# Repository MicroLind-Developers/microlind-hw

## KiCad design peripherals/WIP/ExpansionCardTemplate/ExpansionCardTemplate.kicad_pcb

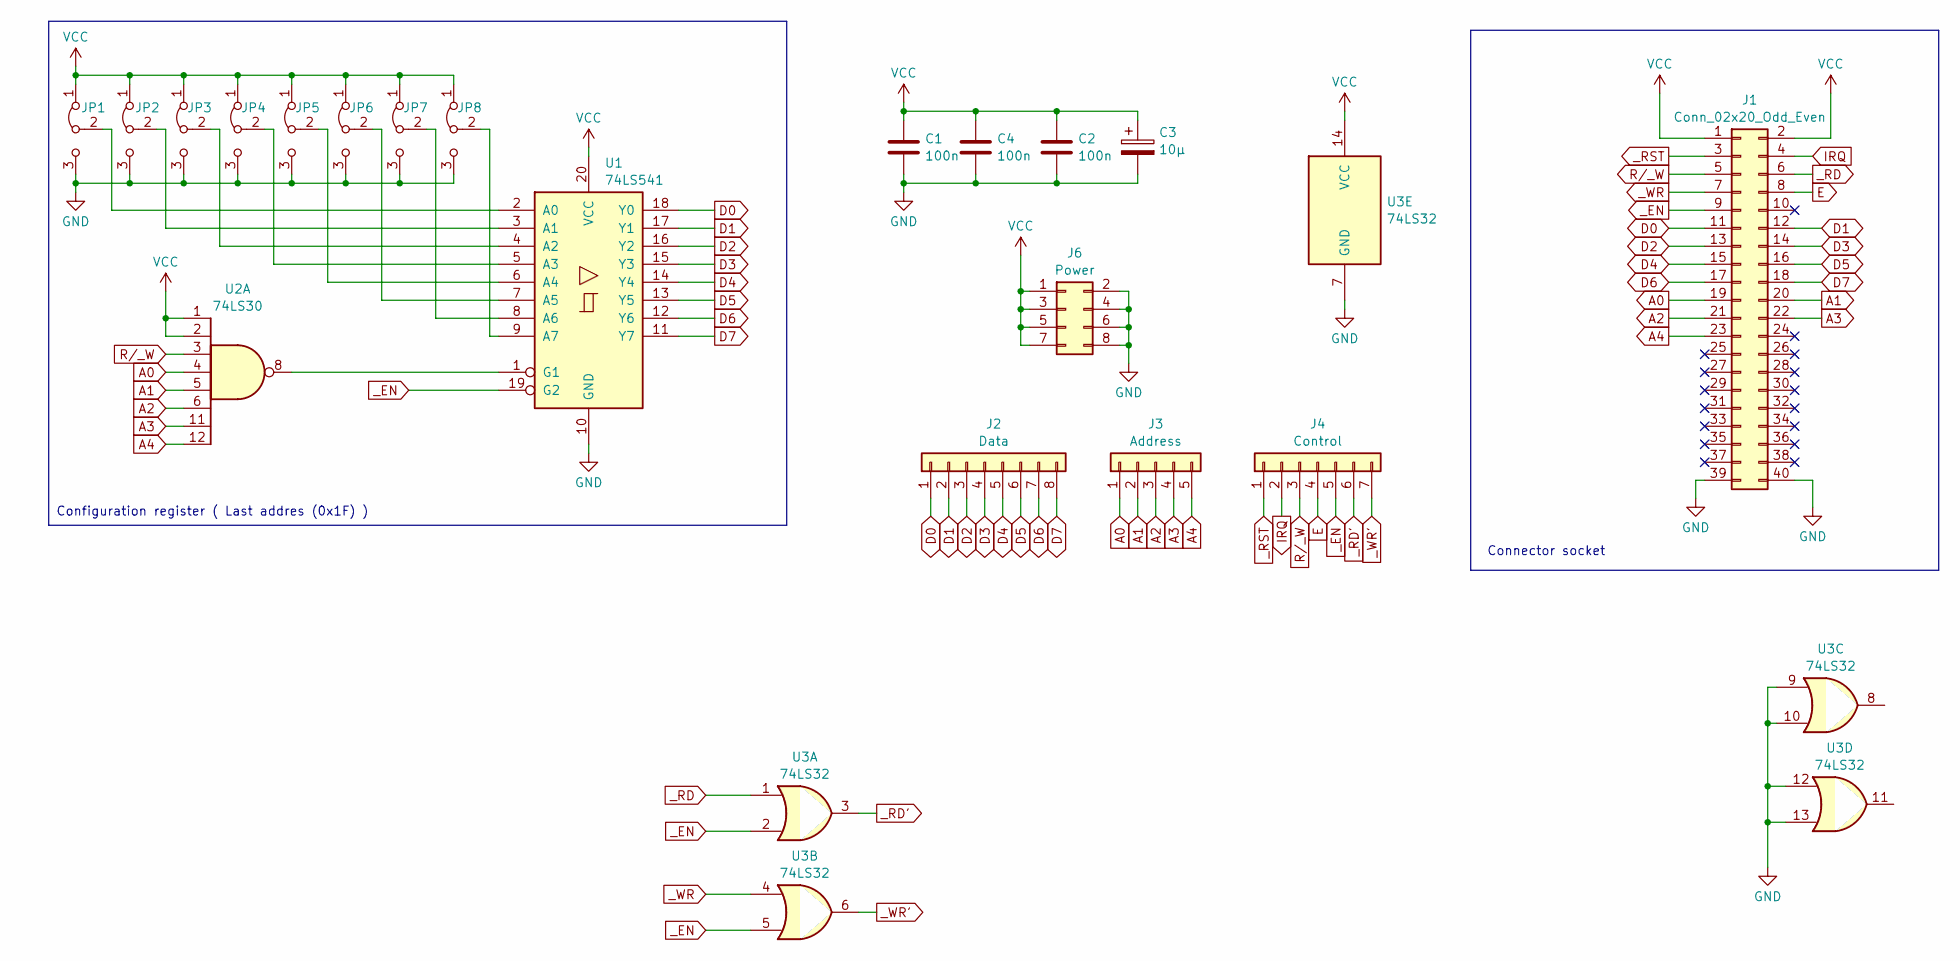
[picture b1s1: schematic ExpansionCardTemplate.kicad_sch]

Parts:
C1, C2, C4: 100n; C_Disc_D3.0mm_W2.0mm_P2.50mm
C3: 10µ; CP_Radial_D4.0mm_P2.00mm
J1: Conn_02x20_Odd_Even; PinHeader_2x20_P2.54mm_Horizontal
J2: Data; PinSocket_1x08_P2.54mm_Vertical
J3: Address; PinSocket_1x05_P2.54mm_Vertical
J4: Control; PinSocket_1x07_P2.54mm_Vertical
J6: Power; PinSocket_2x04_P2.54mm_Vertical
JP1, JP2, JP3, JP4, JP5, JP6, JP7, JP8: Jumper_3_Bridged12; SolderJumper-3_P1.3mm_Open_RoundedPad1.0x1.5mm_NumberLabels
U1: 74LS541; DIP-20_W7.62mm
U2: 74LS30; DIP-12_W7.62mm
U3: 74LS32; DIP-14_W7.62mm

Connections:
A0: J1.19, J3.1, U2.4
A1: J1.20, J3.2, U2.5
A2: J1.21, J3.3, U2.6
A3: J1.22, J3.4, U2.11
A4: J1.23, J3.5, U2.12
D0: J1.11, J2.1, U1.18 (Y0)
D1: J1.12, J2.2, U1.17 (Y1)
D2: J1.13, J2.3, U1.16 (Y2)
D3: J1.14, J2.4, U1.15 (Y3)
D4: J1.15, J2.5, U1.14 (Y4)
D5: J1.16, J2.6, U1.13 (Y5)
D6: J1.17, J2.7, U1.12 (Y6)
D7: J1.18, J2.8, U1.11 (Y7)
E: J1.8, J4.4
GND: C1.2, C2.2, C3.2, C4.2, J1.39, J1.40, J6.2, J6.4, J6.6, J6.8, JP1.3 (B), JP2.3 (B), JP3.3 (B), JP4.3 (B), JP5.3 (B), JP6.3 (B), JP7.3 (B), JP8.3 (B), U1.10 (GND), U3.7 (GND), U3.9, U3.10, U3.12, U3.13
IRQ: J1.4, J4.2
unnamed: JP1.2 (C), U1.2 (A0)
unnamed: JP2.2 (C), U1.3 (A1)
unnamed: JP3.2 (C), U1.4 (A2)
unnamed: JP4.2 (C), U1.5 (A3)
unnamed: JP5.2 (C), U1.6 (A4)
unnamed: JP6.2 (C), U1.7 (A5)
unnamed: JP7.2 (C), U1.8 (A6)
unnamed: JP8.2 (C), U1.9 (A7)
unnamed: U1.1 (G1), U2.8
R/_W: J1.5, J4.3, U2.3
VCC: C1.1, C2.1, C3.1, C4.1, J1.1, J1.2, J6.1, J6.3, J6.5, J6.7, JP1.1 (A), JP2.1 (A), JP3.1 (A), JP4.1 (A), JP5.1 (A), JP6.1 (A), JP7.1 (A), JP8.1 (A), U1.20 (VCC), U2.1, U2.2, U3.14 (VCC)
_EN: J1.9, J4.5, U1.19 (G2), U3.2, U3.5
_RD: J1.6, U3.1
_RD': J4.6, U3.3
_RST: J1.3, J4.1
_WR: J1.7, U3.4
_WR': J4.7, U3.6

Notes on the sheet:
Configuration register ( Last addres (0x1F) )
Connector socket

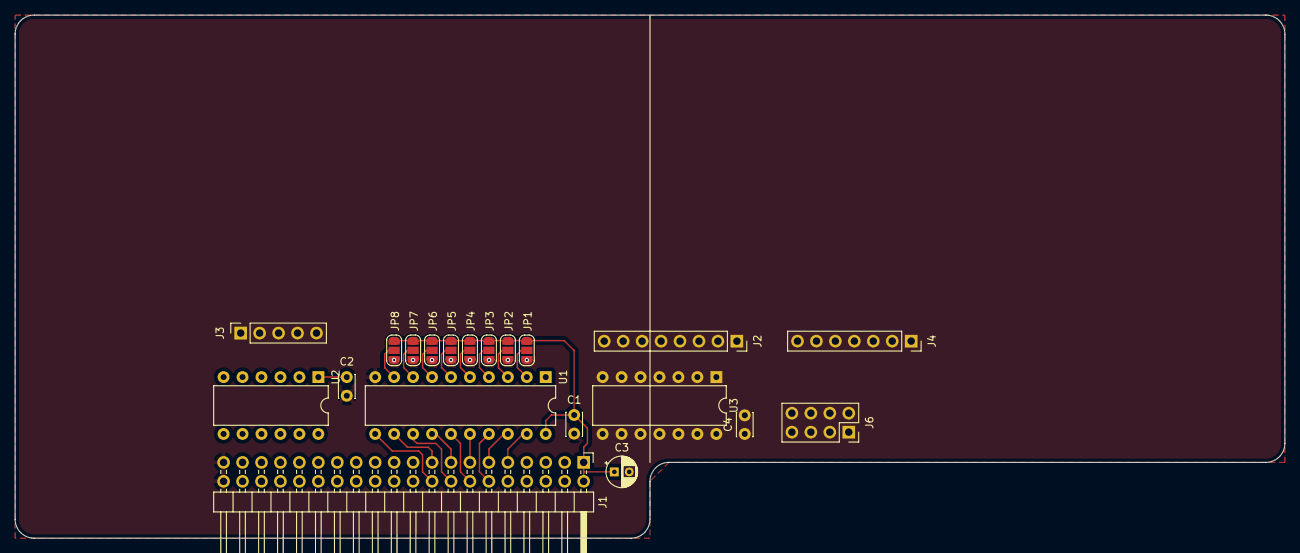
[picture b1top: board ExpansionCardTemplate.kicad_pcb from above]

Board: 2 copper layers, 170.2 x 70.1 mm, 20 parts (0 on the bottom side), 33 nets.

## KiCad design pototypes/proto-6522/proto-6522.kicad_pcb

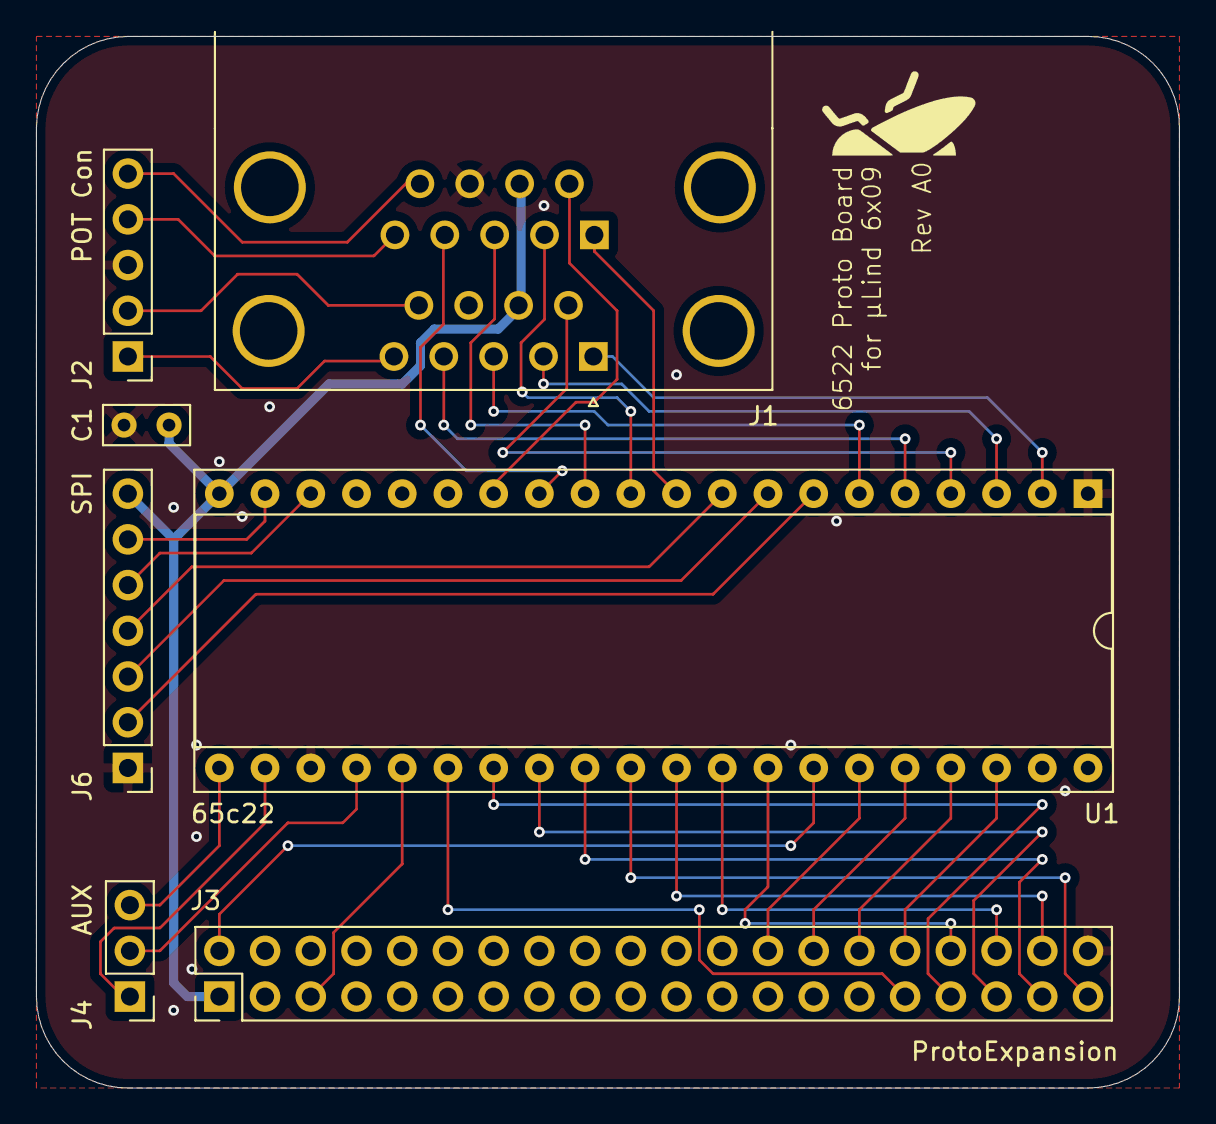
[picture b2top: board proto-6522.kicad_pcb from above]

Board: 2 copper layers, 63.5 x 58.4 mm, 7 parts (0 on the bottom side), 38 nets.

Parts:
C1: C; C_Rect_L4.6mm_W2.0mm_P2.50mm_MKS02_FKP02
J1: DSUB-9-Double_NorComp
J2: POT Con; PinHeader_1x05_P2.54mm_Vertical
J3: ProtoExpansion; PinHeader_2x20_P2.54mm_Vertical
J4: AUX; PinHeader_1x03_P2.54mm_Vertical
J6: SPI; PinHeader_1x07_P2.54mm_Vertical
U1: 65c22; DIP-40_W15.24mm_Socket

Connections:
/A0: J3.32, U1.38 (RS0)
/A1: J3.30, U1.37 (RS1)
/A2: J3.28, U1.36 (RS2)
/A3: J3.26, U1.35 (RS3)
/COPI/CIPO: J6.6, U1.19 (CB2)
/CS0: J6.2, U1.7 (PA5)
/CS1: J6.3, U1.8 (PA6)
/CS2: J6.4, U1.9 (PA7)
/D0: J3.34, U1.33 (D0)
/D1: J3.36, U1.32 (D1)
/D2: J3.38, U1.31 (D2)
/D3: J3.39, U1.30 (D3)
/D4: J3.37, U1.29 (D4)
/D5: J3.35, U1.28 (D5)
/D6: J3.33, U1.27 (D6)
/D7: J3.31, U1.26 (D7)
/E: J3.5, U1.25 (ϕ2)
/R/~W: J4.1, U1.22 (R/~W)
/SCK: J6.5, U1.18 (CB1)
/~INT_PAR: J4.3, U1.21 (~IRQ)
/~PAR_EN: J4.2, U1.24 (CS1)
/~RST: J3.2, U1.34 (~RES)
GND: C1.2, J1.8, J1.18, J2.3, J3.40, J6.1, U1.1 (VSS), U1.23 (~CS2)
unnamed: J1.5, J2.1
unnamed: J1.9, J2.2
unnamed: J1.15, J2.4
unnamed: J1.19, J2.5
unnamed: J1.1, U1.2 (PA0)
unnamed: J1.2, U1.3 (PA1)
unnamed: J1.6, U1.4 (PA2)
unnamed: J1.4, U1.5 (PA3)
unnamed: J1.3, U1.6 (PA4)
unnamed: J1.11, U1.10 (PB0)
unnamed: J1.12, U1.11 (PB1)
unnamed: J1.13, U1.12 (PB2)
unnamed: J1.14, U1.13 (PB3)
unnamed: J1.16, U1.14 (PB4)
VCC: C1.1, J1.7, J1.17, J3.1, J6.7, U1.20 (VCC)

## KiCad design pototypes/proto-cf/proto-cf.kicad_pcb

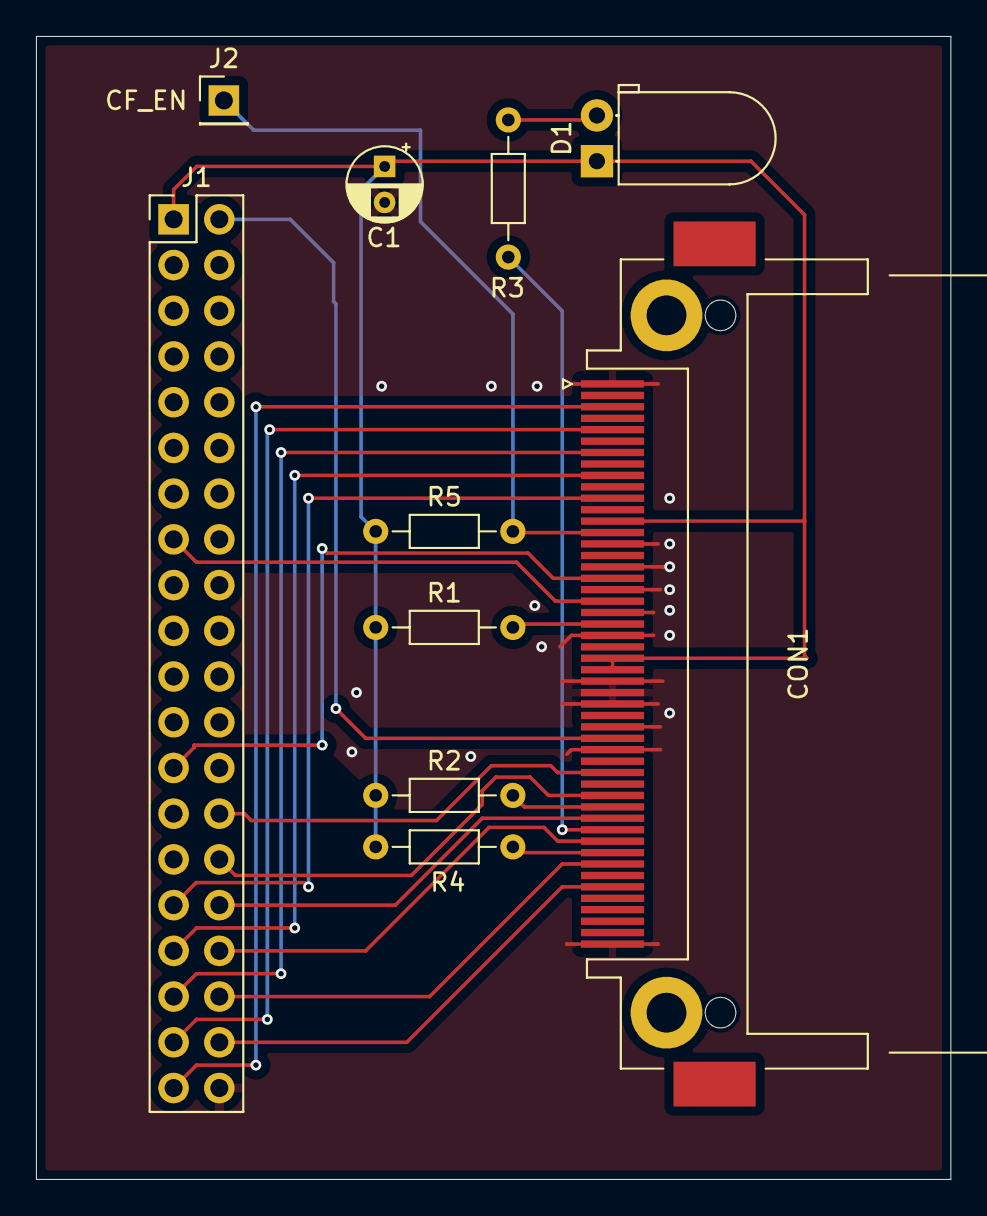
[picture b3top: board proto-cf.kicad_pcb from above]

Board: 2 copper layers, 50.8 x 63.5 mm, 10 parts (0 on the bottom side), 22 nets.

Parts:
C1: C_Polarized; CP_Radial_D4.0mm_P2.00mm
CON1: CF-CARD; CF-Card_3M_N7E50-7516PK-20-WF
D1: LED; LED_D5.0mm_Horizontal_O1.27mm_Z3.0mm_Clear
J1: VideoExpansion; PinHeader_2x20_P2.54mm_Vertical
J2: CF_EN; PinHeader_1x01_P2.54mm_Vertical
R1, R2, R3, R4, R5: 4k7; R_Axial_DIN0204_L3.6mm_D1.6mm_P7.62mm_Horizontal

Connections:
/A0: CON1.20 (A0), J1.32
/A1: CON1.19 (A1), J1.30
/A2: CON1.18 (A2), J1.28
/D0: CON1.21 (D0), J1.34
/D1: CON1.22 (D1), J1.36
/D2: CON1.23 (D2), J1.38
/D3: CON1.2 (D3), J1.39
/D4: CON1.3 (D4), J1.37
/D5: CON1.4 (D5), J1.35
/D6: CON1.5 (D6), J1.33
/D7: CON1.6 (D7), J1.31
/~CF_EN: CON1.32 (/CS1), J2.1, R5.2
/~RD: CON1.34 (/IORD), J1.25
/~RST: CON1.41 (/RESET), J1.2
/~WR: CON1.35 (/IOWR), J1.15
GND: C1.2, CON1.1 (GND1), CON1.8 (A10), CON1.9 (/ATASEL), CON1.10 (A9), CON1.11 (A8), CON1.12 (A7), CON1.14 (A6), CON1.15 (A5), CON1.16 (A4), CON1.17 (A3), CON1.39 (/CSEL), CON1.50 (GND2), J1.40
unnamed: CON1.45 (/DASP), R3.2
unnamed: CON1.46 (/PDIAG), R4.2
unnamed: CON1.44 (/REG), R2.2
unnamed: CON1.36 (/WE), R1.2
unnamed: D1.2 (A), R3.1
VCC: C1.1, CON1.7 (/CS0), CON1.13 (VCC2), CON1.38 (VCC1), D1.1 (K), J1.1, R1.1, R2.1, R4.1, R5.1

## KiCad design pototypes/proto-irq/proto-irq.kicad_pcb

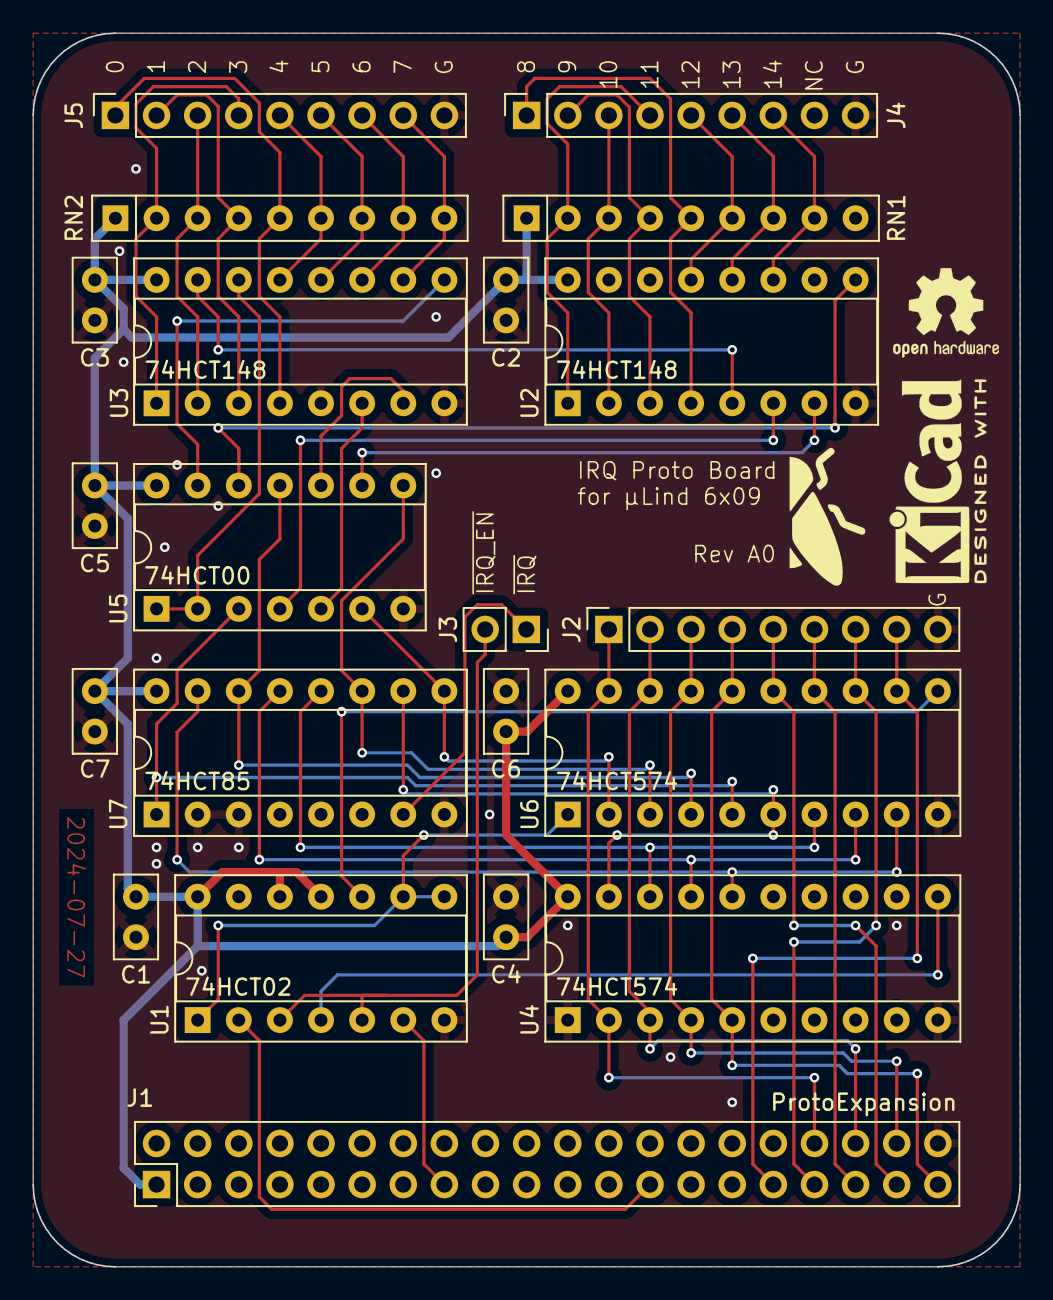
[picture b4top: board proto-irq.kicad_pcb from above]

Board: 2 copper layers, 61.0 x 76.2 mm, 21 parts (0 on the bottom side), 48 nets.

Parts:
C1, C2, C3, C4, C5, C6, C7: 100n; C_Disc_D5.0mm_W2.5mm_P2.50mm
J1: ProtoExpansion; PinHeader_2x20_P2.54mm_Vertical
J2: DataValue; PinSocket_1x09_P2.54mm_Vertical
J3: AUX; PinSocket_1x02_P2.54mm_Vertical
J4: Low IRQ; PinSocket_1x09_P2.54mm_Vertical
J5: High IRQ; PinSocket_1x09_P2.54mm_Vertical
RN1, RN2: R_Network08; R_Array_SIP9
U1: 74HCT02; DIP-14_W7.62mm_Socket
U2, U3: 74HCT148; DIP-16_W7.62mm_Socket
U4, U6: 74HCT574; DIP-20_W7.62mm_Socket
U5: 74HCT00; DIP-14_W7.62mm_Socket
U7: 74HCT85; DIP-16_W7.62mm_Socket

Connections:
/D0: J1.34, J2.1, U4.2 (D0), U6.19 (Q0)
/D1: J1.36, J2.2, U4.3 (D1), U6.18 (Q1)
/D2: J1.38, J2.3, U4.4 (D2), U6.17 (Q2)
/D3: J1.39, J2.4, U4.5 (D3), U6.16 (Q3)
/D4: J1.37, J2.5, U6.15 (Q4)
/D5: J1.35, J2.6, U6.14 (Q5)
/D6: J1.33, J2.7, U6.13 (Q6)
/D7: J1.31, J2.8, U6.12 (Q7)
/~IRQ_EN: J3.2, U1.3, U1.5
/~IRQ: J3.1, U7.7 (Oa<b)
/~RD: J1.25, U1.2
/~WR: J1.15, U1.6
GND: C1.2, C2.2, C3.2, C4.2, C5.2, C6.2, C7.2, J1.40, J2.9, J4.9, J5.9, U1.7 (GND), U2.8 (GND), U3.5 (EI), U3.8 (GND), U4.1 (OE), U4.10 (GND), U5.7 (GND), U6.10 (GND), U7.2 (Ia<b), U7.3 (Ia=b), U7.4 (Ia>b), U7.8 (GND)
unnamed: U2.5 (EI), U3.15 (EO)
unnamed: U2.9 (S0), U5.12
unnamed: U2.7 (S1), U5.9
unnamed: U2.6 (S2), U5.4
unnamed: U3.14 (GS), U5.1, U5.2
unnamed: U3.9 (S0), U5.13
unnamed: U3.7 (S1), U5.10
unnamed: U3.6 (S2), U5.5
unnamed: U1.4, U4.11 (Cp)
unnamed: U4.19 (Q0), U6.6 (D4), U7.10 (A0)
unnamed: U4.18 (Q1), U6.7 (D5), U7.12 (A1)
unnamed: U4.17 (Q2), U6.8 (D6), U7.13 (A2)
unnamed: U4.16 (Q3), U6.9 (D7), U7.15 (A3)
unnamed: U1.10, U6.11 (Cp)
unnamed: U5.6, U6.2 (D0), U7.9 (B0)
unnamed: U5.8, U6.3 (D1), U7.11 (B1)
unnamed: U5.11, U6.4 (D2), U7.14 (B2)
unnamed: U5.3, U6.5 (D3), U7.1 (B3)
unnamed: U1.1, U1.8, U1.9, U6.1 (OE)
VCC: C1.1, C2.1, C3.1, C4.1, C5.1, C6.1, C7.1, J1.1, RN1.1 (common), RN2.1 (common), U1.11, U1.12, U1.14 (VCC), U2.16 (VCC), U3.16 (VCC), U4.20 (VCC), U5.14 (VCC), U6.20 (VCC), U7.16 (VCC)
~IRQ_0: J5.1, RN2.5 (R4), U3.4 (I7)
~IRQ_1: J5.2, RN2.4 (R3), U3.3 (I6)
~IRQ_2: J5.3, RN2.3 (R2), U3.2 (I5)
~IRQ_3: J5.4, RN2.2 (R1), U3.1 (I4)
~IRQ_4: J5.5, RN2.6 (R5), U3.13 (I3)
~IRQ_5: J5.6, RN2.7 (R6), U3.12 (I2)
~IRQ_6: J5.7, RN2.8 (R7), U3.11 (I1)
~IRQ_7: J5.8, RN2.9 (R8), U3.10 (IO)
~IRQ_8: J4.1, RN1.5 (R4), U2.4 (I7)
~IRQ_9: J4.2, RN1.4 (R3), U2.3 (I6)
~IRQ_10: J4.3, RN1.3 (R2), U2.2 (I5)
~IRQ_11: J4.4, RN1.2 (R1), U2.1 (I4)
~IRQ_12: J4.5, RN1.6 (R5), U2.13 (I3)
~IRQ_13: J4.6, RN1.7 (R6), U2.12 (I2)
~IRQ_14: J4.7, RN1.8 (R7), U2.11 (I1)

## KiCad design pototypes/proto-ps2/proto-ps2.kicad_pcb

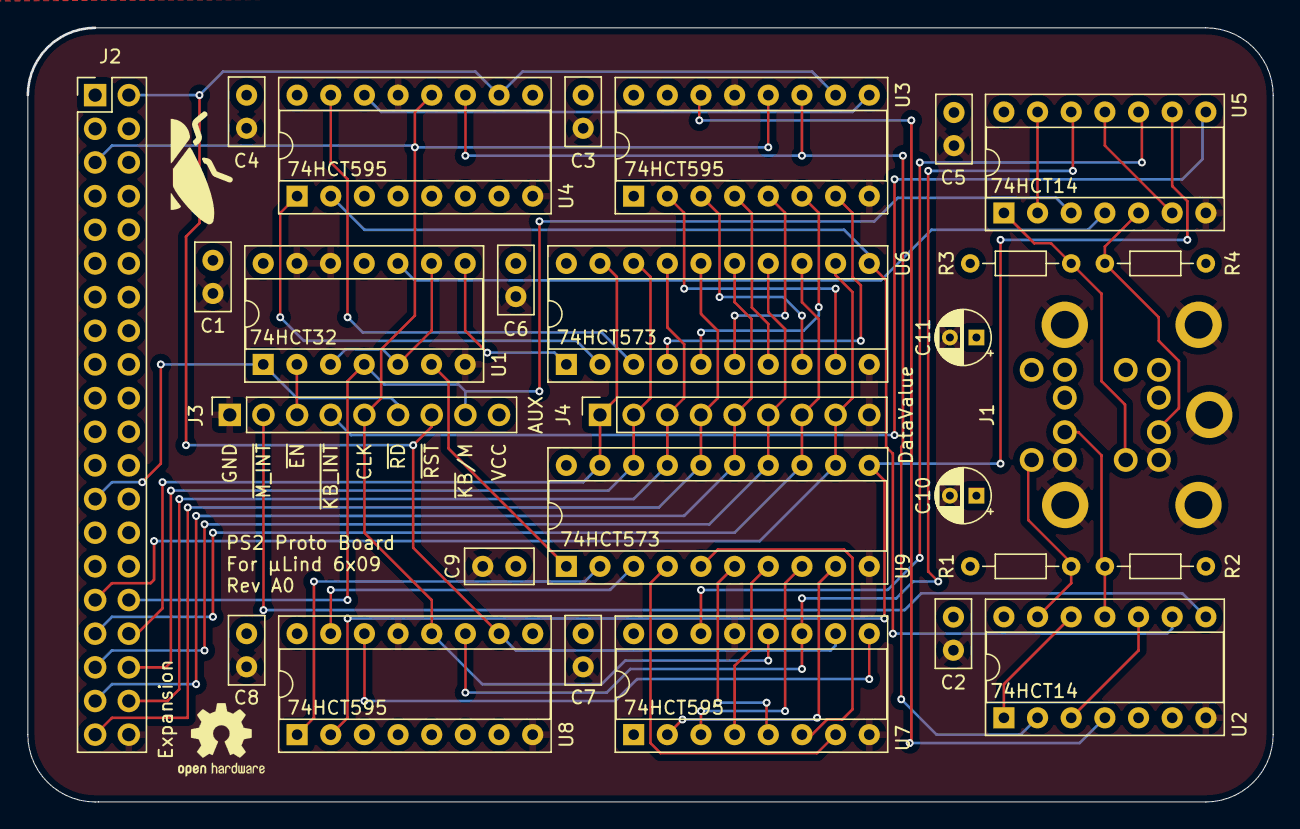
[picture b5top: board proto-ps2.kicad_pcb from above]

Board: 4 copper layers, 94.0 x 58.4 mm, 28 parts (0 on the bottom side), 53 nets.

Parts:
C1, C2, C3, C4, C5, C6, C7, C8, C9: 100n; C_Disc_D5.0mm_W2.5mm_P2.50mm
C10, C11: 10u; CP_Radial_D4.0mm_P2.00mm
J1: 2xPS2-Mini-Din
J2: Expansion; PinHeader_2x20_P2.54mm_Vertical
J3: AUX; PinSocket_1x09_P2.54mm_Vertical
J4: DataValue; PinSocket_1x09_P2.54mm_Vertical
R1, R2, R3, R4: 10k; R_Axial_DIN0204_L3.6mm_D1.6mm_P7.62mm_Horizontal
U1: 74HCT32; DIP-14_W7.62mm_Socket
U2, U5: 74HCT14; DIP-14_W7.62mm_Socket
U3, U4, U7, U8: 74HCT595; DIP-16_W7.62mm_Socket
U6, U9: 74HCT573; DIP-20_W7.62mm_Socket

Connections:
/D0: J2.34, J4.1, U6.19 (Q0), U9.19 (Q0)
/D1: J2.36, J4.2, U6.18 (Q1), U9.18 (Q1)
/D2: J2.38, J4.3, U6.17 (Q2), U9.17 (Q2)
/D3: J2.39, J4.4, U6.16 (Q3), U9.16 (Q3)
/D4: J2.37, J4.5, U6.15 (Q4), U9.15 (Q4)
/D5: J2.35, J4.6, U6.14 (Q5), U9.14 (Q5)
/D6: J2.33, J4.7, U6.13 (Q6), U9.13 (Q6)
/D7: J2.31, J4.8, U6.12 (Q7), U9.12 (Q7)
/E: J2.5, J3.5, U3.12 (RCLK), U4.12 (RCLK), U7.12 (RCLK), U8.12 (RCLK)
/M_CLK: U2.2, U3.11 (SRCLK), U4.11 (SRCLK)
/M_DATA: U2.4, U3.14 (SER)
/PS2_KB_CLK: J1.11 (Kbd_Clock), R3.2, U5.1
/PS2_KB_DATA: J1.7 (Kbd_Data), R4.2, U5.5
/PS2_M_CLK: J1.5 (Mouse_Clock), R1.2, U2.13
/PS2_M_DATA: J1.1 (Mouse_Data), R2.2, U2.11
/~INT_PS2_KB: J3.4, U5.8
/~INT_PS2_M: J3.2, U2.8
/~PS2_EN: J3.3, U1.2
/~RD: J2.25, J3.6, U1.1
/~RST: J2.2, J3.7, U3.10 (~SRCLR), U4.10 (~SRCLR), U7.10 (~SRCLR), U8.10 (~SRCLR)
A0: J2.32, J3.8, U1.4, U5.3
GND: C1.2, C2.2, C3.2, C4.2, C5.2, C6.2, C7.2, C8.2, C9.2, C10.2, C11.2, J1.3 (Mouse_GND), J1.9 (Kbd_GND), J1.G (GND), J2.40, J3.1, J4.9, U1.7 (GND), U1.12, U1.13, U2.7 (GND), U3.8 (GND), U3.13 (~OE), U4.8 (GND), U4.13 (~OE), U5.7 (GND), U6.10 (GND), U7.8 (GND), U7.13 (~OE), U8.8 (GND), U8.13 (~OE), U9.10 (GND)
unnamed: U1.3, U1.5, U1.9
unnamed: U1.10, U5.4
unnamed: U2.1, U2.12
unnamed: U2.3, U2.10
unnamed: U3.2 (QC), U6.9 (D7)
unnamed: U3.3 (QD), U6.8 (D6)
unnamed: U3.4 (QE), U6.7 (D5)
unnamed: U3.5 (QF), U6.6 (D4)
unnamed: U3.6 (QG), U6.5 (D3)
unnamed: U3.9 (QH'), U4.14 (SER)
unnamed: U3.7 (QH), U6.4 (D2)
unnamed: U4.15 (QA), U6.3 (D1)
unnamed: U4.1 (QB), U6.2 (D0)
unnamed: U2.9, U4.2 (QC), U6.11 (Load)
unnamed: U5.6, U5.11
unnamed: U5.2, U5.13
unnamed: U1.8, U6.1 (OE)
unnamed: U7.2 (QC), U9.9 (D7)
unnamed: U7.3 (QD), U9.8 (D6)
unnamed: U7.4 (QE), U9.7 (D5)
unnamed: U7.5 (QF), U9.6 (D4)
unnamed: U7.6 (QG), U9.5 (D3)
unnamed: U7.9 (QH'), U8.14 (SER)
unnamed: U7.7 (QH), U9.4 (D2)
unnamed: U5.10, U7.14 (SER)
unnamed: U5.12, U7.11 (SRCLK), U8.11 (SRCLK)
unnamed: U8.15 (QA), U9.3 (D1)
unnamed: U8.1 (QB), U9.2 (D0)
unnamed: U5.9, U8.2 (QC), U9.11 (Load)
unnamed: U1.6, U9.1 (OE)
VCC: C1.1, C2.1, C3.1, C4.1, C5.1, C6.1, C7.1, C8.1, C9.1, C10.1, C11.1, J1.4 (Mouse_PWR), J1.10 (Kbd_PWR), J2.1, J3.9, R1.1, R2.1, R3.1, R4.1, U1.14 (VCC), U2.5, U2.14 (VCC), U3.16 (VCC), U4.16 (VCC), U5.14 (VCC), U6.20 (VCC), U7.16 (VCC), U8.16 (VCC), U9.20 (VCC)

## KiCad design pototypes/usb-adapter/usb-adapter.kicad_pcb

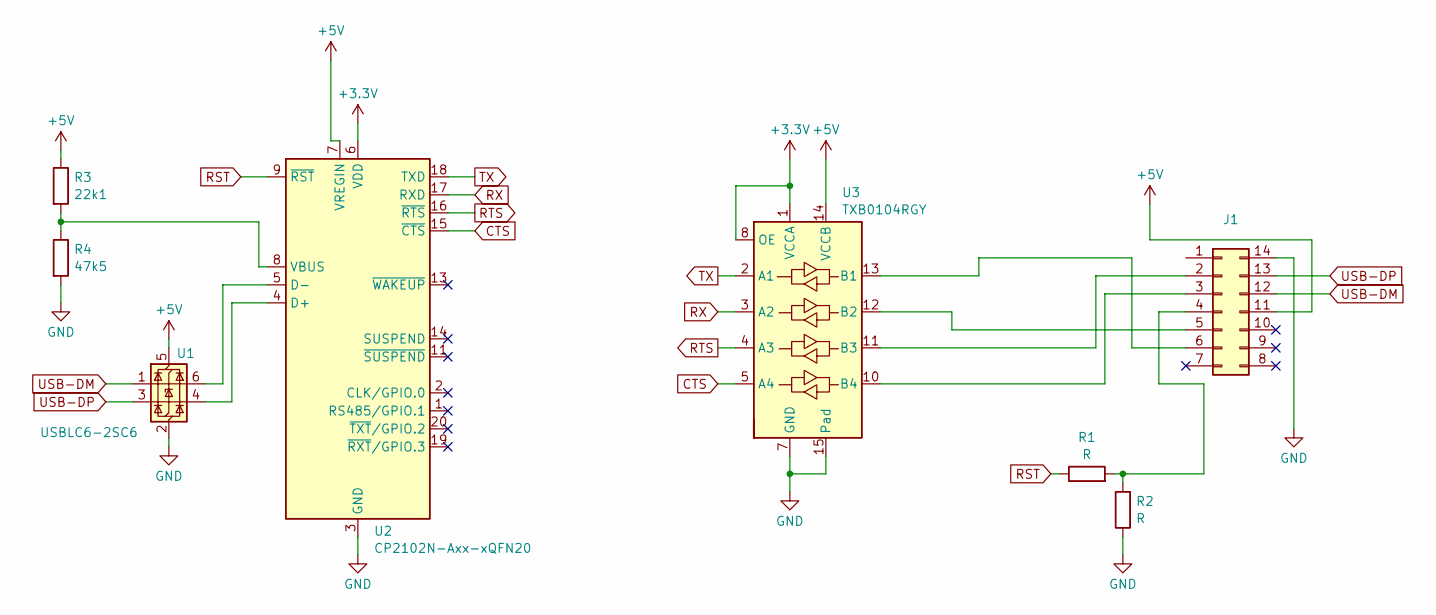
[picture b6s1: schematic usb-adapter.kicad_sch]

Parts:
J1: Conn_02x07_Counter_Clockwise; DIP-14_W7.62mm
R1, R2: R; R_0402_1005Metric_Pad0.72x0.64mm
R3: 22k1; R_0402_1005Metric_Pad0.72x0.64mm
R4: 47k5; R_0402_1005Metric_Pad0.72x0.64mm
U1: USBLC6-2SC6; SOT-23-6
U2: CP2102N-Axx-xQFN20; SiliconLabs_QFN-20-1EP_3x3mm_P0.5mm
U3: TXB0104RGY; Texas_S-PVQFN-N14

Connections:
+3.3V: U2.6 (VDD), U3.1 (VCCA), U3.8 (OE)
+5V: J1.11, R3.1, U1.5 (VBUS), U2.7 (VREGIN), U3.14 (VCCB)
CTS: U2.15 (~CTS), U3.5 (A4)
GND: J1.14, R2.1, R4.2, U1.2 (GND), U2.3 (GND), U2.12 (GND), U2.21 (GND), U3.7 (GND), U3.15 (Pad)
unnamed: J1.2, U3.11 (B3)
unnamed: J1.3, U3.10 (B4)
unnamed: J1.4, R1.2, R2.2
unnamed: J1.5, U3.12 (B2)
unnamed: J1.6, U3.13 (B1)
unnamed: U1.4 (I/O2), U2.4 (D+)
unnamed: U1.6 (I/O1), U2.5 (D-)
unnamed: R3.2, R4.1, U2.8 (VBUS)
RST: R1.1, U2.9 (~RST)
RTS: U2.16 (~RTS), U3.4 (A3)
RX: U2.17 (RXD), U3.3 (A2)
TX: U2.18 (TXD), U3.2 (A1)
USB-DM: J1.12, U1.1 (I/O1)
USB-DP: J1.13, U1.3 (I/O2)

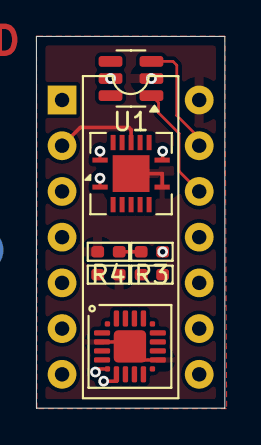
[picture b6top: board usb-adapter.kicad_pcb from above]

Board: 6 copper layers, 10.5 x 20.7 mm, 8 parts (0 on the bottom side), 18 nets.

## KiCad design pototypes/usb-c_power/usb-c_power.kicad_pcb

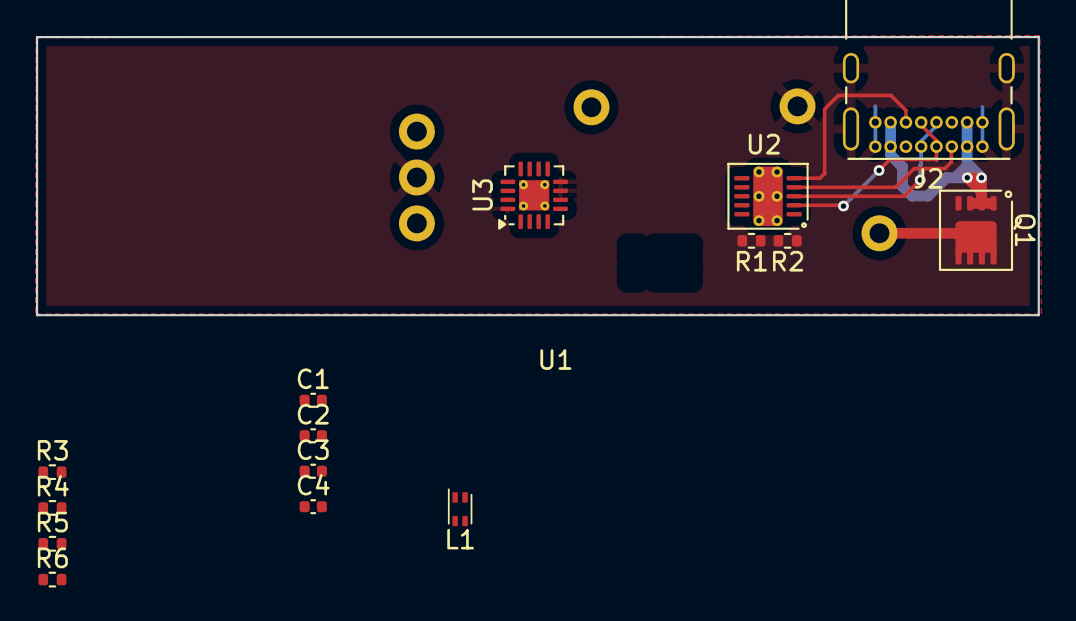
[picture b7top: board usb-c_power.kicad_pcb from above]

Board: 2 copper layers, 55.7 x 15.5 mm, 16 parts (0 on the bottom side), 17 nets.

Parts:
C1: C; C_0402_1005Metric
C2: 10u; C_0402_1005Metric
C3: 3.3n; C_0402_1005Metric
C4: 22u; C_0402_1005Metric
J2: USB_C_Receptacle_USB2.0_14P; USB_C_Receptacle_GCT_USB4085
L1: 2.2uH; L_CommonModeChoke_Coilcraft_0603USB
Q1: AONR21307; Infineon_PG_TSDSON-8
R1, R4: 5k1; R_0402_1005Metric
R2: 49k9; R_0402_1005Metric
R3: 10; R_0402_1005Metric
R5: 10k; R_0402_1005Metric
R6: 16k5; R_0402_1005Metric
U1: usb-c_power
U2: DFN-10-1EP_3x3mm_P0.5mm_EP1.65x2.38mm_ThermalVias2
U3: TPS62143; VQFN-16-1EP_3x3mm_P0.5mm_EP1.68x1.68mm_ThermalVias

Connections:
GND: C1.2, C2.2, C3.2, C4.2, J2.A1 (GND), J2.A12 (GND), J2.B1 (GND), J2.B12 (GND), J2.S1 (SHIELD), R5.2, R6.2, U1.2 (GND), U1.5 (GND), U3.6 (GND), U3.7 (FSW), U3.8 (DEF), U3.15 (GND), U3.16 (GND), U3.17 (GND)
unnamed: J2.A5 (CC1), U2.4 (CC1)
unnamed: J2.B5 (CC2), U2.5 (CC2)
unnamed: J2.A4 (VBUS), J2.A9 (VBUS), J2.B4 (VBUS), J2.B9 (VBUS), Q1.1 (S), Q1.2 (S), Q1.3 (S), R2.1, R3.1
unnamed: L1.1, U3.1 (SW), U3.2 (SW), U3.3 (SW)
unnamed: Q1.5 (D), U1.8 (VOut)
unnamed: Q1.4 (G), R1.1, R2.2
unnamed: C4.1, L1.2, R4.2, U1.1 (+5v), U3.14 (VOS)
unnamed: C2.1, U1.3 (Vin), U1.4 (+12v), U3.10 (VIN), U3.11 (VIN), U3.12 (VIN), U3.13 (EN)
unnamed: J2.A6 (D+), J2.B6 (D+), U2.2 (D+)
unnamed: J2.A7 (D-), J2.B7 (D-), U2.3 (D-)
unnamed: R1.2, U2.10 (Gate)
unnamed: R6.1, U2.9 (ISET)
unnamed: R5.1, U2.8 (VSET)
unnamed: C1.1, R3.2, U2.1 (Vin)
unnamed: R4.1, U3.4 (PG)
unnamed: C3.1, U3.9 (SS/TR)

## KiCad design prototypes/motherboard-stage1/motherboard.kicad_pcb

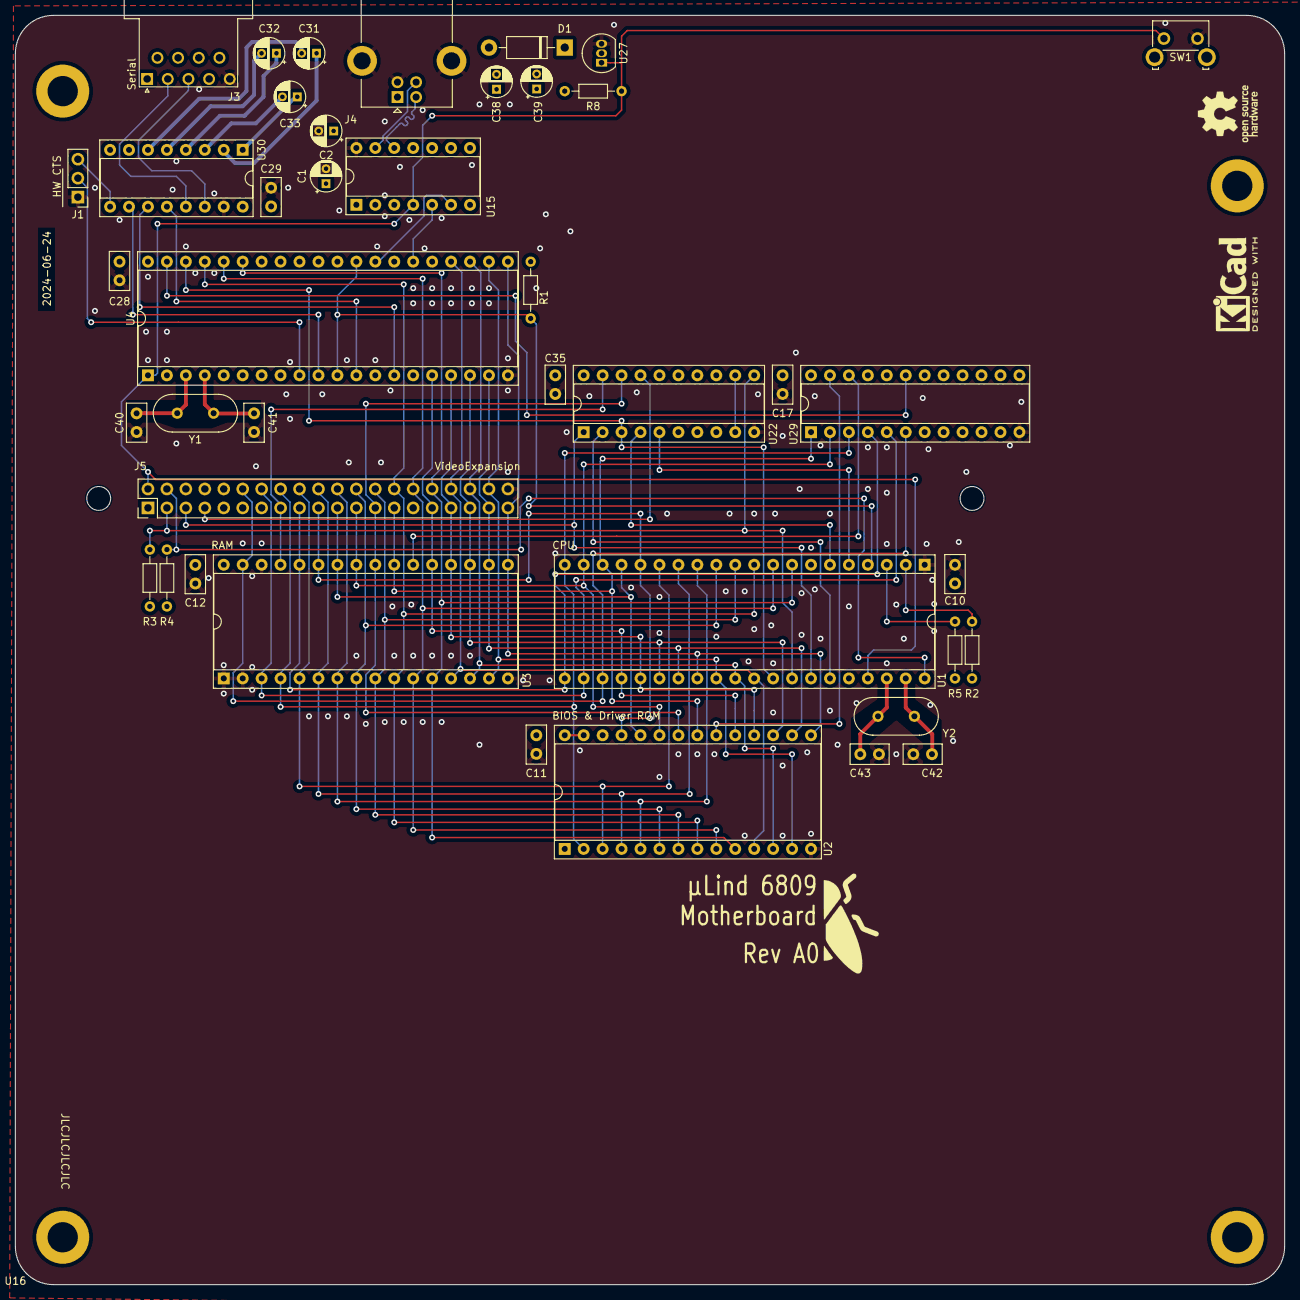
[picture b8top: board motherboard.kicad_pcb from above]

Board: 4 copper layers, 170.2 x 170.2 mm, 44 parts (0 on the bottom side), 69 nets.

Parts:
C1, C2, C31, C32, C33: 1u; CP_Radial_D4.0mm_P2.00mm
C10, C11, C12, C17, C28, C29, C35: C; C_Disc_D5.0mm_W2.5mm_P2.50mm
C38: 100µF; CP_Radial_D4.0mm_P2.00mm
C39: 10µF; CP_Radial_D4.0mm_P2.00mm
C40, C41: 43pF; C_Disc_D5.0mm_W2.5mm_P2.50mm
C42, C43: 24pF; C_Disc_D5.0mm_W2.5mm_P2.50mm
D1: 1N4007; D_DO-41_SOD81_P10.16mm_Horizontal
H6, H8: MountingHole; MountingHole_3.2mm_M3_ISO7380
J1: HW CTS; PinHeader_1x03_P2.54mm_Vertical
J3: Serial; DSUB-9_Female_Horizontal_P2.77x2.84mm_EdgePinOffset9.40mm
J4: Console; USB_B_Lumberg_2411_02_Horizontal
J5: VideoExpansion; PinHeader_2x20_P2.54mm_Vertical
R1, R2, R3, R4, R5, R8: 4k7; R_Axial_DIN0204_L3.6mm_D1.6mm_P7.62mm_Horizontal
SW1: Reset; SW_SPST_Omron_B3F-315x_Angled
U1: MC6809; DIP-40_W15.24mm_Socket
U2: 28C64; DIP-28_W15.24mm_Socket
U3: AS6C4008; DIP-32_W15.24mm_Socket
U4: DIP-40_W15.24mm_Socket
U15: MCP2221A; DIP-14_W7.62mm_Socket
U16: mITX
U22: GAL16V8; DIP-20_W7.62mm_Socket
U27: DS1813; TO-92_Inline
U29: GAL 22V10; DIP-24_W7.62mm_Socket
U30: MAX232; DIP-16_W7.62mm_Socket
Y1, Y2: Crystal; Crystal_HC49-U_Vertical

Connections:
/A0: J5.32, U1.8 (A0), U2.10 (A0), U3.12 (A0), U4.35 (RS0)
/A1: J5.30, U1.9 (A1), U2.9 (A1), U3.11 (A1), U4.36 (RS1)
/A2: J5.28, U1.10 (A2), U2.8 (A2), U3.10 (A2), U4.37 (RS2)
/A3: J5.26, U1.11 (A3), U2.7 (A3), U3.9 (A3)
/A4: J5.24, U1.12 (A4), U2.6 (A4), U3.8 (A4)
/A5: J5.22, U1.13 (A5), U2.5 (A5), U3.7 (A5)
/A6: J5.20, U1.14 (A6), U2.4 (A6), U3.6 (A6)
/A7: J5.18, U1.15 (A7), U2.3 (A7), U3.5 (A7)
/A8: J5.19, U1.16 (A8), U2.25 (A8), U3.27 (A8)
/A9: J5.21, U1.17 (A9), U2.24 (A9), U3.26 (A9)
/A10: J5.27, U1.18 (A10), U2.21 (A10), U3.23 (A10), U29.1 (I1/CLK)
/A11: J5.23, U1.19 (A11), U2.23 (A11), U3.25 (A11), U29.2 (I2)
/A12: J5.16, U1.20 (A12), U2.2 (A12), U3.4 (A12), U29.3 (I3)
/A13: J5.17, U1.21 (A13), U3.28 (A13), U29.4 (I4)
/A14: J5.14, U1.22 (A14), U3.3 (A14), U29.5 (I5)
/A15: J5.12, U1.23 (A15), U3.31 (A15), U29.6 (I6)
/Address-Logic/BA: U1.6 (BA), U22.4 (I4)
/Address-Logic/BS: U1.5 (BS), U22.5 (I5)
/Address-Logic/Q: U1.35 (Q), U22.2 (I2)
/Address-Logic/R/~W: U1.32 (R/~W), U4.38 (R~W), U22.3 (I3)
/Address-Logic/~RAM_EN: U3.22 (CE#), U29.22 (IO2)
/Address-Logic/~ROM_EN: U2.20 (~CE), U29.23 (IO1)
/Address-Logic/~SER_EN: U4.39 (~CS), U29.19 (IO5)
/CPU_MEM/~FIRQ: R1.1, U1.4 (~FIRQ), U4.11 (~IRQ2), U4.29 (~IRQ1)
/CPU_MEM/~HALT: J5.4, R4.1, U1.40 (~HALT)
/CPU_MEM/~IRQ: R5.1, U1.3 (~IRQ)
/CPU_MEM/~NMI: R2.1, U1.2 (~NMI)
/D0: J5.34, U1.31 (D0), U2.11 (D0), U3.13 (DQ0), U4.24 (D0)
/D1: J5.36, U1.30 (D1), U2.12 (D1), U3.14 (DQ1), U4.23 (D1)
/D2: J5.38, U1.29 (D2), U2.13 (D2), U3.15 (DQ2), U4.22 (D2)
/D3: J5.39, U1.28 (D3), U2.15 (D3), U3.17 (DQ3), U4.21 (D3)
/D4: J5.37, U1.27 (D4), U2.16 (D4), U3.18 (DQ4), U4.19 (D4)
/D5: J5.35, U1.26 (D5), U2.17 (D5), U3.19 (DQ5), U4.18 (D5)
/D6: J5.33, U1.25 (D6), U2.18 (D6), U3.20 (DQ6), U4.17 (D6)
/D7: J5.31, U1.24 (D7), U2.19 (D7), U3.21 (DQ7), U4.16 (D7)
/Expansion Ports/BAVAIL: J5.7, U22.17 (I03)
/Expansion Ports/E: J5.5, U1.34 (E), U22.1 (I1/CLK)
/Expansion Ports/~BREQ: J5.3, R3.1, U1.33 (~DMA/BREQ), U22.11 (I10/~OE)
/Expansion Ports/~RD: J5.25, U2.22 (~OE), U3.24 (OE#), U22.18 (IO2)
/Expansion Ports/~RST: J5.2, R8.2, SW1.1, U1.37 (~RESET), U4.1 (~RST), U15.4 (~RST), U27.1 (~RST)
/Expansion Ports/~WR: J5.15, U3.29 (WE#), U22.19 (IO1)
/Serial-Parallel/D+: J4.3 (D+), U15.13 (D+)
/Serial-Parallel/D-: J4.2 (D-), U15.12 (D-)
GND: C1.2, C2.2, C10.2, C11.2, C12.2, C17.2, C28.2, C29.2, C35.2, C40.2, C41.2, C42.2, C43.2, J1.1, J3.5, J4.4 (GND), J4.5 (Shield), J5.40, SW1.2, U1.1 (VSS), U2.14 (GND), U3.1 (A18), U3.2 (A16), U3.16 (VSS), U3.30 (A17), U4.20 (Vss), U15.14 (VSS), U22.10 (GND), U27.3 (GND), U29.12 (GND), U30.15 (GND)
unnamed: J1.2, U4.9 (~CTS2)
unnamed: J1.3, U30.9 (R2OUT)
unnamed: C43.1, U1.38 (EXTAL), Y2.1
unnamed: C42.1, U1.39 (XTAL), Y2.2
unnamed: C40.1, U4.3 (X1), Y1.2
unnamed: C41.1, U4.4 (X2), Y1.1
unnamed: U4.26 (TxD1), U15.5 (URx)
unnamed: U4.28 (RxD1), U15.6 (UTx)
unnamed: C2.1, U15.11 (VUSB)
unnamed: C33.1, U30.1 (C1+)
unnamed: C33.2, U30.3 (C1-)
unnamed: C32.1, U30.4 (C2+)
unnamed: C32.2, U30.5 (C2-)
unnamed: J3.2, U30.13 (R1IN)
unnamed: U4.12 (RxD2), U30.12 (R1OUT)
unnamed: J3.8, U30.8 (R2IN)
unnamed: U4.14 (TxD2), U30.11 (T1IN)
unnamed: J3.3, U30.14 (T1OUT)
unnamed: U4.10 (~RTS2), U30.10 (T2IN)
unnamed: J3.7, U30.7 (T2OUT)
unnamed: C31.1, U30.2 (VS+)
unnamed: C31.2, U30.6 (VS-)
VBUS: C1.1, C38.1, C39.1, D1.2 (A), J4.1 (VBUS), U15.1 (VDD)
VCC: C10.1, C11.1, C12.1, C17.1, C28.1, C29.1, C35.1, C38.2, C39.2, D1.1 (K), J5.1, R1.2, R2.2, R3.2, R4.2, R5.2, R8.1, U1.7 (VCC), U2.27 (~WE), U2.28 (VCC), U3.32 (VCC), U4.40 (VCC), U22.20 (VCC), U27.2 (VCC), U29.24 (VCC), U30.16 (VCC)
~RD': U22.9 (I9), U22.12 (IO8)
